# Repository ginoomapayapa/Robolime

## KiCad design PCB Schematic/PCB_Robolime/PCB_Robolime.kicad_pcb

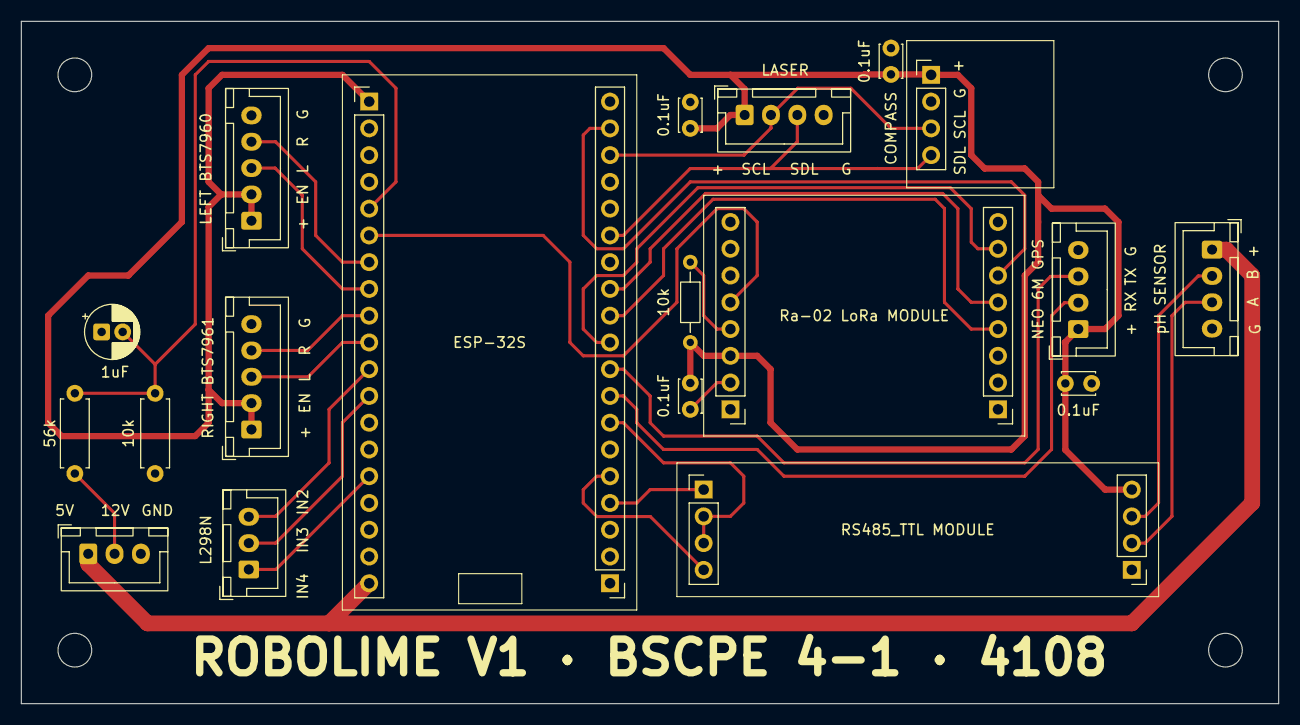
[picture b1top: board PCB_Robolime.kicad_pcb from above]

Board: 2 copper layers, 119.4 x 64.8 mm, 22 parts (0 on the bottom side), 28 nets.

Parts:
0.1uF, 0.1uF#2, 0.1uF#3, 0.1uF#4: C; C_Disc_D3.0mm_W2.0mm_P2.50mm
1uF: C_Polarized; CP_Radial_D5.0mm_P2.00mm
5V: Conn_01x03_Socket; JST_XH_B3B-XH-A_1x03_P2.50mm_Vertical
10k: R; R_Axial_DIN0204_L3.6mm_D1.6mm_P7.62mm_Horizontal
10k#2: 10k; R_Axial_DIN0207_L6.3mm_D2.5mm_P7.62mm_Horizontal
56k: 56k; R_Axial_DIN0207_L6.3mm_D2.5mm_P7.62mm_Horizontal
COMPASS: Conn_01x04_Socket; PinHeader_1x04_P2.54mm_Vertical
ESP-32S: Conn_01x19_Socket; PinHeader_1x19_P2.54mm_Vertical
L298N: Conn_01x03_Socket; JST_XH_B3B-XH-A_1x03_P2.50mm_Vertical
LASER: Conn_01x04_Socket; JST_XH_B4B-XH-A_1x04_P2.50mm_Vertical
LEFT BTS7960: Conn_01x05_Socket; JST_XH_B5B-XH-A_1x05_P2.50mm_Vertical
NEO 6M GPS: Conn_01x04_Socket; JST_XH_B4B-XH-A_1x04_P2.50mm_Vertical
RIGHT BTS7961: Conn_01x05_Socket; JST_XH_B5B-XH-A_1x05_P2.50mm_Vertical
RIGHT_ESP32: Conn_01x19_Socket; PinHeader_1x19_P2.54mm_Vertical
RIGHT_LoRa1: Conn_01x08_Socket; PinHeader_1x08_P2.54mm_Vertical
RS485_TTL MODULE, RS485_TTL-PHPINS1: Conn_01x04_Socket; PinHeader_1x04_P2.54mm_Vertical
Ra-02 LoRa MODULE: Conn_01x08_Socket; PinHeader_1x08_P2.54mm_Vertical
pH SENSOR: Conn_01x04_Socket; JST_XH_B4B-XH-A_1x04_P2.50mm_Vertical

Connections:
/3V ESP32: 0.1uF.1, 0.1uF#2.1, 0.1uF#3.1, 0.1uF#4.1, 10k.2, COMPASS.1, ESP-32S.1, LASER.1, LEFT BTS7960.1, LEFT BTS7960.2, NEO 6M GPS.1, RIGHT BTS7961.1, RIGHT BTS7961.2, RS485_TTL-PHPINS1.4, Ra-02 LoRa MODULE.3
/5V SUPPLY: 5V.1, ESP-32S.19, pH SENSOR.1
/12V SUPPLY: 5V.2, 56k.1
/BATT Voltage Reading: 1uF.2, 10k#2.1, 56k.2, ESP-32S.5
/Compass SCL: COMPASS.3, LASER.2, RIGHT_ESP32.17
/Compass SDA: COMPASS.4, LASER.3, RIGHT_ESP32.14
/GPS RX: NEO 6M GPS.2, RIGHT_ESP32.8
/GPS TX: NEO 6M GPS.3, RIGHT_ESP32.9
/L298N Act_E IN4: ESP-32S.15, L298N.1
/L298N Act_R IN3: ESP-32S.12, L298N.2
/L298N Pump IN2: ESP-32S.11, L298N.3
/LEFT BTS7960 LPWM: ESP-32S.8, LEFT BTS7960.3
/LEFT BTS7960 RPWM: ESP-32S.7, LEFT BTS7960.4
/LoRa DIO0: ESP-32S.6, Ra-02 LoRa MODULE.5
/LoRa MISO: RIGHT_ESP32.12, RIGHT_LoRa1.5
/LoRa MOSI: RIGHT_ESP32.18, RIGHT_LoRa1.6
/LoRa NSS: RIGHT_ESP32.10, RIGHT_LoRa1.7
/LoRa SCK: RIGHT_ESP32.11, RIGHT_LoRa1.4
/RIGHT BTS7960 LPWM: ESP-32S.10, RIGHT BTS7961.3
/RIGHT BTS7960 RPWM: ESP-32S.9, RIGHT BTS7961.4
/RS485 DI: RIGHT_ESP32.5, RS485_TTL MODULE.4
/RS485 RE/DE: RIGHT_ESP32.7, RS485_TTL MODULE.2, RS485_TTL MODULE.3
/RS485 RO: RIGHT_ESP32.4, RS485_TTL MODULE.1
GND: 0.1uF.2, 0.1uF#2.2, 0.1uF#4.2, 1uF.1, 5V.3, 10k#2.2, COMPASS.2, LASER.4, LEFT BTS7960.5, NEO 6M GPS.4, RIGHT BTS7961.5, RIGHT_ESP32.19, RIGHT_LoRa1.1, RS485_TTL-PHPINS1.1, pH SENSOR.4
unnamed: 0.1uF#3.2, Ra-02 LoRa MODULE.2
unnamed: 10k.1, Ra-02 LoRa MODULE.4
unnamed: RS485_TTL-PHPINS1.2, pH SENSOR.3
unnamed: RS485_TTL-PHPINS1.3, pH SENSOR.2
